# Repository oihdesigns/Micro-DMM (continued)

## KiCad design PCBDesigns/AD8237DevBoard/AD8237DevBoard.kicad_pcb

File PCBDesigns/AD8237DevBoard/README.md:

# AD8237 Sensor Development Board - Rev C

KiCad 10, 60 x 50 mm, two layers. Eight I2C-selected gains, buffered half-supply reference, 3.3 V or 5 V analog supply.

Open `AD8237DevBoard.kicad_pro`. Nick's edited PCB is the layout source. Rev C replaces U2 and adds nine resistors. Existing placements are retained except C10, moved slightly to clear the larger mux. The pre-change design is in `archive/pre-eight-gain/`.

**Prototype:** not fabricated or measured. Electrical/layout checks and ideal DC calculations do not establish measured stability, noise, settling or accuracy.

## Eight gains

U2: **TMUX1108PWR**, PW TSSOP-16, 4.4 x 5 mm body, 0.65 mm pitch. U3: **TCA9536DGKR**, I2C address **0x41**. P0/P1/P2 drive A0/A1/A2; P3 is unused. No range-bank jumper is needed.

| Code / A2 A1 A0 | Nominal gain | Upper resistor | Lower resistor | U2 channel / pin |
|---|---:|---|---|---|
| 0 / 000 | 1 | R13 2k sense resistor | None | S1 / 4 |
| 1 / 001 | 2.5 | R21 30k | R22 20k | S2 / 5 |
| 2 / 010 | 5.02 | R23 40.2k | R24 10k | S3 / 6 |
| 3 / 011 | 10.09 | R4 90.9k | R3 10k | S4 / 7 |
| 4 / 100 | 25.048096 | R25 120k | R26 4.99k | S5 / 12 |
| 5 / 101 | 49.780488 | R27 100k | R28 2.05k | S6 / 11 |
| 6 / 110 | 101 | R6 100k | R5 1k | S7 / 10 |
| 7 / 111 | 1001 | R12 1M | R11 1k | S8 / 9 |

Upper resistors run from OUT_RAW to the selected tap; lower resistors run from the tap to REF. Gain resistors are 0.1% thin film, <=25 ppm/degree C, 0805. The original 10.09/101/1001 resistor pairs are retained. The mux selects a high-impedance feedback node, keeping switch on-resistance out of the gain-setting resistor ratio.

Initialize U3 in this order:

1. Write register `0x01 = 0x00`: preload unity into the output latch.
2. Write register `0x03 = 0xF0`: P0-P3 outputs; unused P3 stays low, avoiding a floating input when pull-ups are disabled.
3. Write register `0x50 = 0x40`: disable internal port pull-ups.

Then write code 0-7 to register `0x01`, updating all selection bits together. **The code mapping changed from Rev B:** code 1 is now 2.5, not 10.09.

R17/R18/R29 are 4.7k pull-downs: the maximum specified 100 uA internal startup pull-up current produces <=0.475 V including resistor tolerance. EN is tied high; VSS is grounded. After valid supplies establish, the default is unity before software initialization. Reinitialize after VIO power cycling; a host reset alone does not reset a separately powered U3.

The Arduino Wire example is `firmware/AD8237GainExample/AD8237GainExample.ino`. It starts at unity and accepts a serial digit 0-7. Its 50 ms startup and 20 ms gain-change delays are initial bench-test allowances, not guaranteed settling times. Discard ADC samples during switching and settling. The example has not been compiled for a particular controller or tested on hardware.

## Connections

| Connector | Pins in order |
|---|---|
| J1 | 1 external regulated analog supply, 2 GND |
| J2 | 1 IN+, 2 IN-, 3 GND |
| J3 | 1 OUT after R8, 2 GND, 3 external reference |
| J4 | 1 GND, 2 host VIO supply, 3 SDA, 4 SCL |

| Jumper | Default | Alternative |
|---|---|---|
| JP1 | 2-3: analog supply from VIO | 1-2: analog supply from J1 |
| JP2 | **1-2: LOW bandwidth** | 2-3: HIGH only while gain >=10 |
| JP3 | 3-4: buffered VS/2 | 1-2: GND; 5-6: external J3 reference |
| JP4 | Fitted: 4.7k I2C pull-ups to VIO | Remove if host has suitable pull-ups |

Fit one shunt on each JP1/JP2/JP3, plus JP4 as appropriate. Change supply/reference shunts with power off. **Keep JP2 LOW for normal eight-gain operation and startup.** HIGH is unsuitable at gains 1, 2.5 and 5.02. With JP2 empty, R7 pulls BW low.

For normal 3.3 V use, power J4 VIO at 3.3 V and select JP1 2-3. For 5 V analog with a 3.3 V controller, power J1 from regulated 5 V, J4 VIO from 3.3 V, and select JP1 1-2. The mux accepts 3.3 V controls with a 5 V supply. Always match VIO to the host logic voltage. A 5 V analog output can exceed a 3.3 V ADC's input range.

## Analog behavior

`VOUT_RAW = VREF + G * (VIN+ - VIN-)`, before output resistor R8.

OPA333 U4 buffers a filtered equal-10k divider, giving about 1.65 V at VS=3.3 V or 2.5 V at VS=5 V. Selected REF drives all seven divider returns; R14 connects it to the AD8237 REF pin. External references must be low impedance and able to source and sink divider current.

The seven dividers present about 12.7k from OUT_RAW to REF. Prefer an output load of **100k or greater**: effective load is then about 11.3k, above the AD8237's recommended 10k. At 1.65 V output-reference difference, divider current is about 130 uA. R8 adds about 0.1% attenuation into 100k; TP5 senses before R8. Individual feedback divider Thevenin resistances are below 30k.

At gain 1001 and REF=1.65 V, +/-1 mV differential input ideally gives 0.649-2.651 V output. Both physical inputs must remain within supply limits. Allow output headroom and calibrate for resistor ratios, temperature and amplifier/load errors.

C7 stays fitted at 470 pF C0G, following AD8237 Figure 76. The TMUX1108 has higher feedback-node capacitance than the former mux. LOW bandwidth is the baseline; bench-check overshoot, oscillation and settling at every gain. No device-level transient simulation or measured stability margin is claimed.

C3-C6 and R9/R10 are DNP by default. They provide optional filters and input bias-current returns. Floating sensors need an appropriate DC return. C7 and the remaining resistors/capacitors are fitted.

## Deliverables and checks

- `docs/AD8237DevBoard-schematic.pdf`: current schematic.
- `docs/ERC.json`, `docs/DRC.json`, `docs/design-verification.json`: electrical, routing/parity and independent pin/gain verification.
- `manufacturing/BOM.csv`, `manufacturing/placement.csv`: current assembly data.
- `manufacturing/AD8237DevBoard-RevC-Gerbers.zip`: current fabrication package.
- `manufacturing/stencil/`: paste with DNP parts omitted.

General routing uses 0.20 mm tracks/clearance. A local 0.15 mm pad-clearance override on U3 accommodates that standard package's pad gaps. Other footprints retain the project clearance rule.

`scripts/export.ps1` checks and exports the edited board. `scripts/design.py` regenerates the schematic from component data, preserving existing project settings; it does not ingest manual schematic changes. The old full-board builder is disabled to protect the edited PCB. The one-time migration writes only a draft under `tmp/eight-gain/`.

## Datasheet references

- [AD8237](https://www.analog.com/media/en/technical-documentation/data-sheets/ad8237.pdf): pinout p8, gain/BW p20, programmable gain Figure 76 p25.
- [TMUX1108](https://www.ti.com/lit/ds/symlink/tmux1108.pdf): PW pinout p2-3, supply and logic ratings, truth table p23.
- [TCA9536](https://www.ti.com/lit/ds/symlink/tca9536.pdf): DGK pins, startup pull-ups, address and registers p19-20.
- [OPA333](https://www.ti.com/lit/ds/symlink/opa333.pdf): SOT-23 pinout and buffer operation.

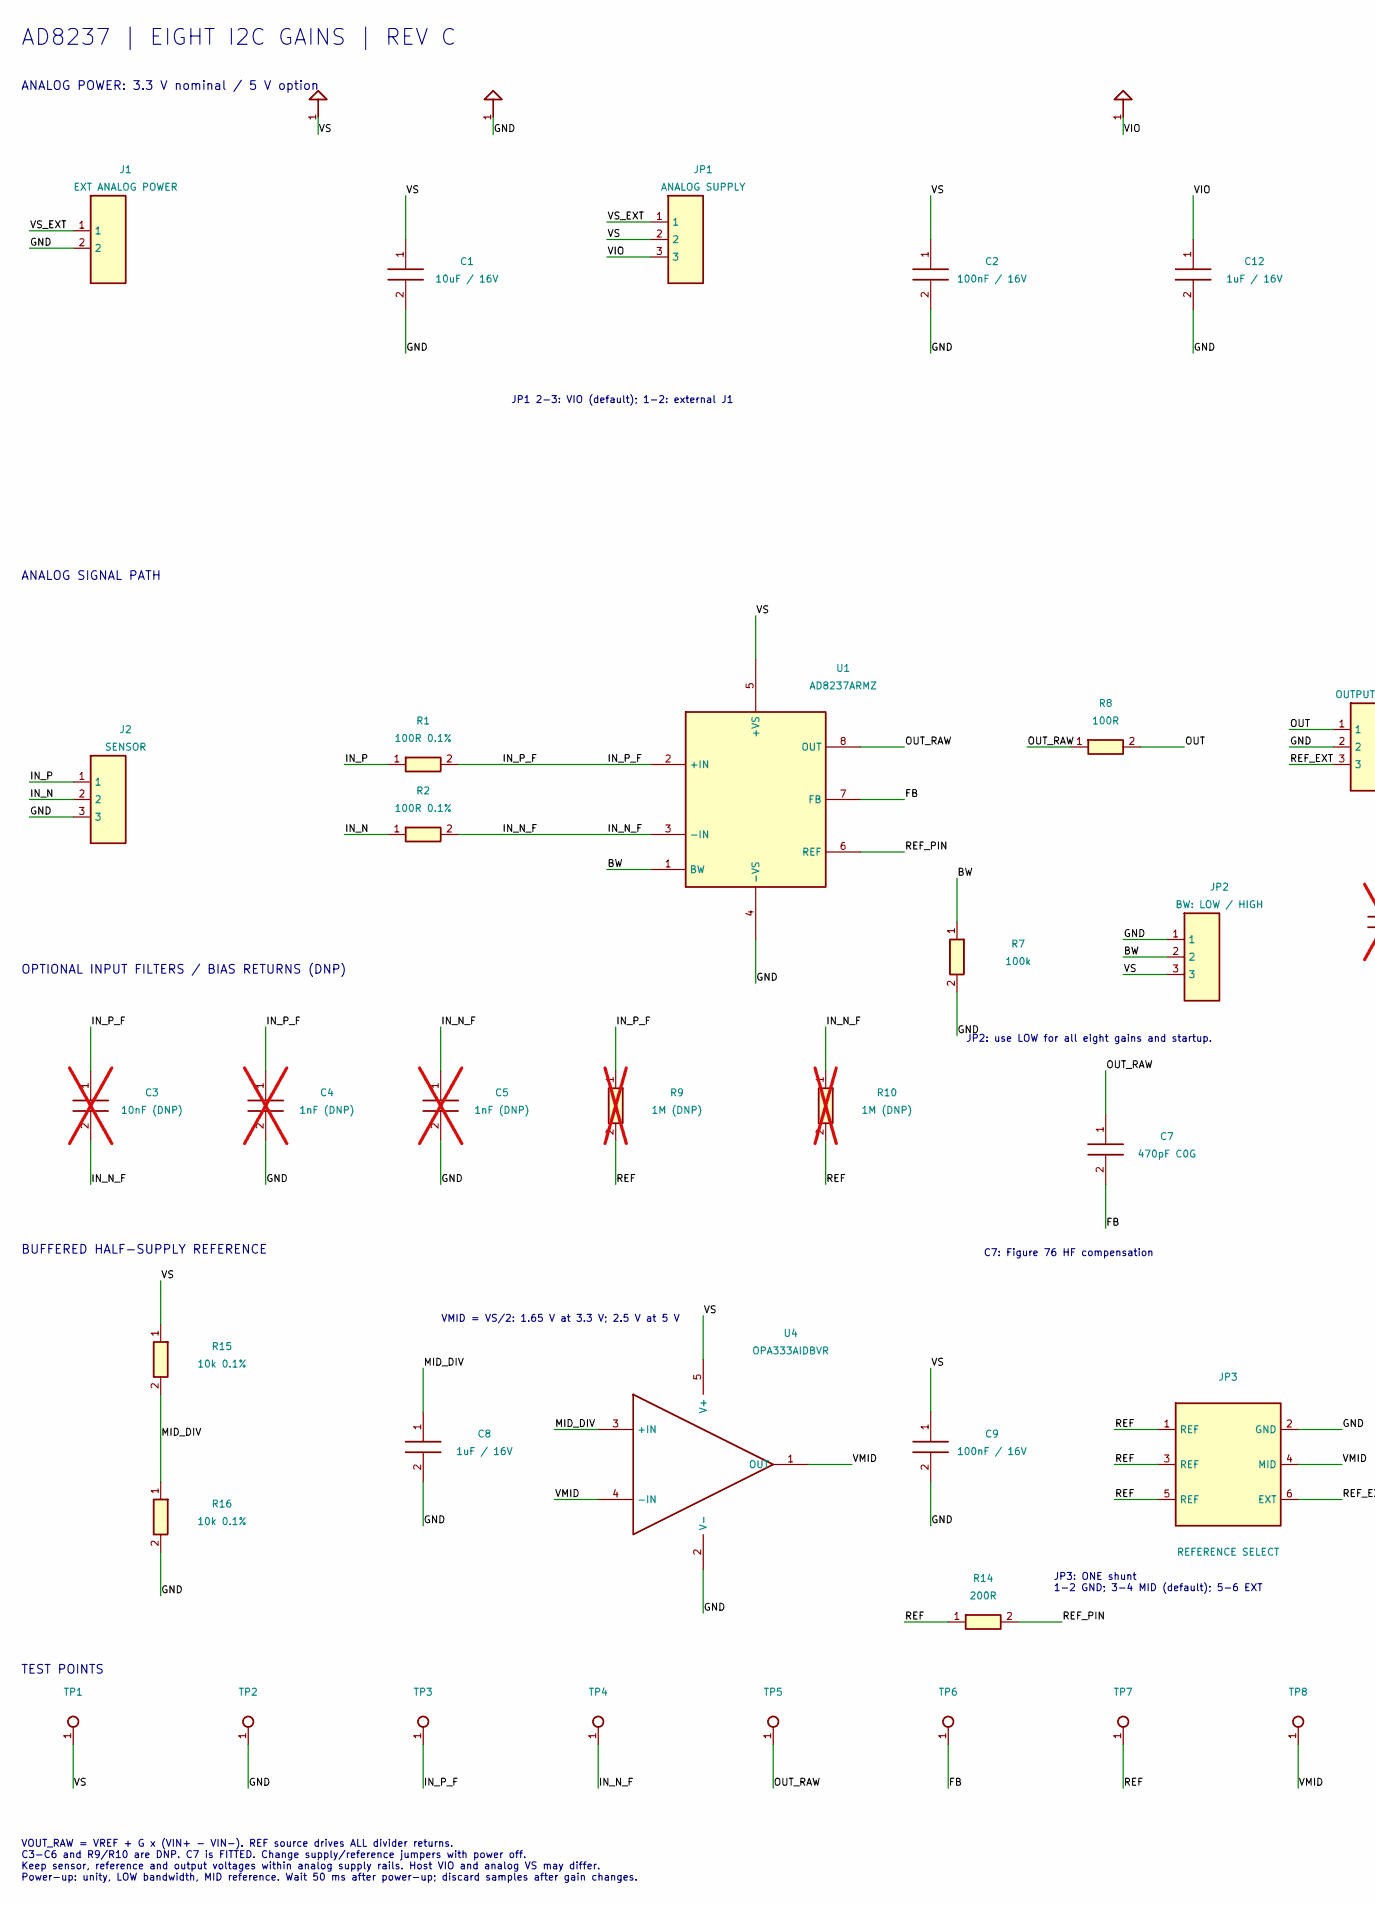
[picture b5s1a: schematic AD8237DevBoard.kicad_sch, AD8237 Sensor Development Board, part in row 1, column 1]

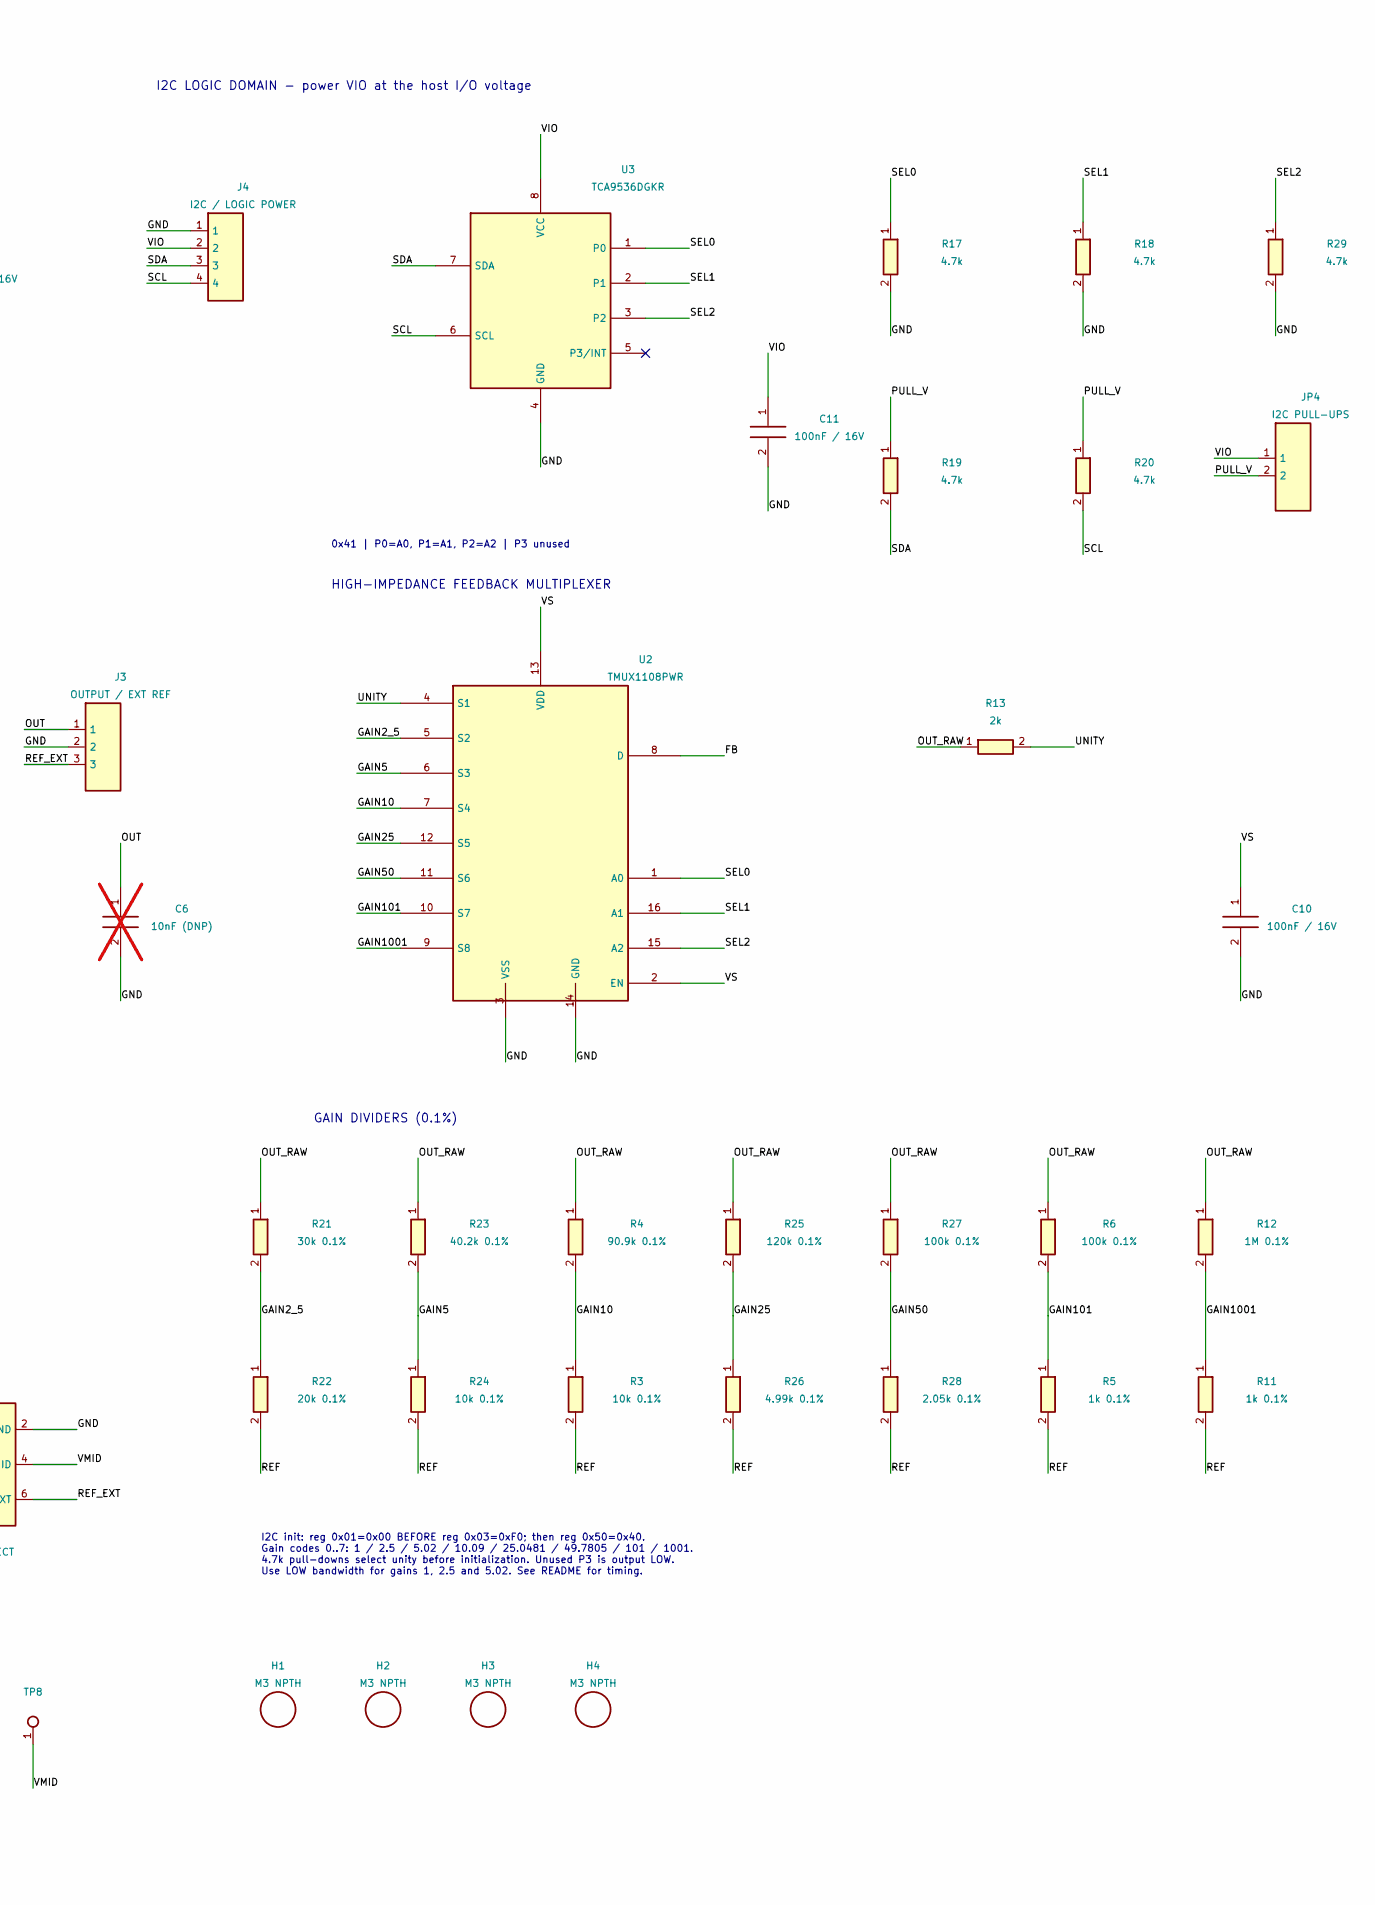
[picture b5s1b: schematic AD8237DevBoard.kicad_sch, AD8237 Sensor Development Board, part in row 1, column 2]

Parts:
C1: 10uF / 16V; C_0805_2012Metric
C2, C9, C10, C11: 100nF / 16V; C_0805_2012Metric
C3, C6: 10nF (DNP); C_0805_2012Metric; not fitted
C4, C5: 1nF (DNP); C_0805_2012Metric; not fitted
C7: 470pF C0G; C_0805_2012Metric
C8, C12: 1uF / 16V; C_0805_2012Metric
H1, H2, H3, H4: M3 NPTH; MountingHole_3.2mm_M3
J1: EXT ANALOG POWER; PinHeader_1x02_P2.54mm_Vertical
J2: SENSOR; PinHeader_1x03_P2.54mm_Vertical
J3: OUTPUT / EXT REF; PinHeader_1x03_P2.54mm_Vertical
J4: I2C / LOGIC POWER; PinHeader_1x04_P2.54mm_Vertical
JP1: ANALOG SUPPLY; PinHeader_1x03_P2.54mm_Vertical
JP2: BW: LOW / HIGH; PinHeader_1x03_P2.54mm_Vertical
JP3: REFERENCE SELECT; PinHeader_2x03_P2.54mm_Vertical
JP4: I2C PULL-UPS; PinHeader_1x02_P2.54mm_Vertical
R1, R2: 100R 0.1%; R_0805_2012Metric
R3, R15, R16, R24: 10k 0.1%; R_0805_2012Metric
R4: 90.9k 0.1%; R_0805_2012Metric
R5, R11: 1k 0.1%; R_0805_2012Metric
R6, R27: 100k 0.1%; R_0805_2012Metric
R7: 100k; R_0805_2012Metric
R8: 100R; R_0805_2012Metric
R9, R10: 1M (DNP); R_0805_2012Metric; not fitted
R12: 1M 0.1%; R_0805_2012Metric
R13: 2k; R_0805_2012Metric
R14: 200R; R_0805_2012Metric
R17, R18, R19, R20, R29: 4.7k; R_0805_2012Metric
R21: 30k 0.1%; R_0805_2012Metric
R22: 20k 0.1%; R_0805_2012Metric
R23: 40.2k 0.1%; R_0805_2012Metric
R25: 120k 0.1%; R_0805_2012Metric
R26: 4.99k 0.1%; R_0805_2012Metric
R28: 2.05k 0.1%; R_0805_2012Metric
TP1: VS; TestPoint_Pad_D1.5mm
TP2: GND; TestPoint_Pad_D1.5mm
TP3: IN_P_F; TestPoint_Pad_D1.5mm
TP4: IN_N_F; TestPoint_Pad_D1.5mm
TP5: OUT_RAW; TestPoint_Pad_D1.5mm
TP6: FB; TestPoint_Pad_D1.5mm
TP7: REF; TestPoint_Pad_D1.5mm
TP8: VMID; TestPoint_Pad_D1.5mm
U1: AD8237ARMZ; MSOP-8_3x3mm_P0.65mm
U2: TMUX1108PWR; TSSOP-16_4.4x5mm_P0.65mm
U3: TCA9536DGKR; VSSOP-8_3x3mm_P0.65mm
U4: OPA333AIDBVR; SOT-23-5

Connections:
/BW: JP2.2, R7.1, U1.1 (BW)
/FB: C7.2, TP6.1, U1.7 (FB), U2.8 (D)
/GAIN2_5: R21.2, R22.1, U2.5 (S2)
/GAIN5: R23.2, R24.1, U2.6 (S3)
/GAIN10: R3.1, R4.2, U2.7 (S4)
/GAIN25: R25.2, R26.1, U2.12 (S5)
/GAIN50: R27.2, R28.1, U2.11 (S6)
/GAIN101: R5.1, R6.2, U2.10 (S7)
/GAIN1001: R11.1, R12.2, U2.9 (S8)
/GND: C1.2, C2.2, C4.2, C5.2, C6.2, C8.2, C9.2, C10.2, C11.2, C12.2, J1.2, J2.3, J3.2, J4.1, JP2.1, JP3.2 (GND), R7.2, R16.2, R17.2, R18.2, R29.2, TP2.1, U1.4 (-VS), U2.3 (VSS), U2.14 (GND), U3.4 (GND), U4.2 (V-)
/IN_N: J2.2, R2.1
/IN_N_F: C3.2, C5.1, R2.2, R10.1, TP4.1, U1.3 (-IN)
/IN_P: J2.1, R1.1
/IN_P_F: C3.1, C4.1, R1.2, R9.1, TP3.1, U1.2 (+IN)
/MID_DIV: C8.1, R15.2, R16.1, U4.3 (+IN)
/OUT: C6.1, J3.1, R8.2
/OUT_RAW: C7.1, R4.1, R6.1, R8.1, R12.1, R13.1, R21.1, R23.1, R25.1, R27.1, TP5.1, U1.8 (OUT)
/PULL_V: JP4.2, R19.1, R20.1
/REF: JP3.1 (REF), JP3.3 (REF), JP3.5 (REF), R3.2, R5.2, R9.2, R10.2, R11.2, R14.1, R22.2, R24.2, R26.2, R28.2, TP7.1
/REF_EXT: J3.3, JP3.6 (EXT)
/REF_PIN: R14.2, U1.6 (REF)
/SCL: J4.4, R20.2, U3.6 (SCL)
/SDA: J4.3, R19.2, U3.7 (SDA)
/SEL0: R17.1, U2.1 (A0), U3.1 (P0)
/SEL1: R18.1, U2.16 (A1), U3.2 (P1)
/SEL2: R29.1, U2.15 (A2), U3.3 (P2)
/UNITY: R13.2, U2.4 (S1)
/VIO: C11.1, C12.1, J4.2, JP1.3, JP4.1, U3.8 (VCC)
/VMID: JP3.4 (MID), TP8.1, U4.1 (OUT), U4.4 (-IN)
/VS: C1.1, C2.1, C9.1, C10.1, JP1.2, JP2.3, R15.1, TP1.1, U1.5 (+VS), U2.2 (EN), U2.13 (VDD), U4.5 (V+)
/VS_EXT: J1.1, JP1.1

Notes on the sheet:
AD8237 | EIGHT I2C GAINS | REV C
ANALOG POWER: 3.3 V nominal / 5 V option
JP1 2-3: VIO (default); 1-2: external J1
I2C LOGIC DOMAIN - power VIO at the host I/O voltage
0x41 | P0=A0, P1=A1, P2=A2 | P3 unused
ANALOG SIGNAL PATH
HIGH-IMPEDANCE FEEDBACK MULTIPLEXER
JP2: use LOW for all eight gains and startup.
OPTIONAL INPUT FILTERS / BIAS RETURNS (DNP)
C7: Figure 76 HF compensation
GAIN DIVIDERS (0.1%)
BUFFERED HALF-SUPPLY REFERENCE
VMID = VS/2: 1.65 V at 3.3 V; 2.5 V at 5 V
JP3: ONE shunt 1-2 GND; 3-4 MID (default); 5-6 EXT
I2C init: reg 0x01=0x00 BEFORE reg 0x03=0xF0; then reg 0x50=0x40. Gain codes 0..7: 1 / 2.5 / 5.02 / 10.09 / 25.0481 / 49.7805 / 101 / 1001. 4.7k pull-downs select unity before initialization. Unused P3 is output LOW. Use LOW bandwidth for gains 1, 2.5 and 5.02. See README for timing.
TEST POINTS
VOUT_RAW = VREF + G x (VIN+ - VIN-). REF source drives ALL divider returns. C3-C6 and R9/R10 are DNP. C7 is FITTED. Change supply/reference jumpers with power off. Keep sensor, reference and output voltages within analog supply rails. Host VIO and analog VS may differ. Power-up: unity, LOW bandwidt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

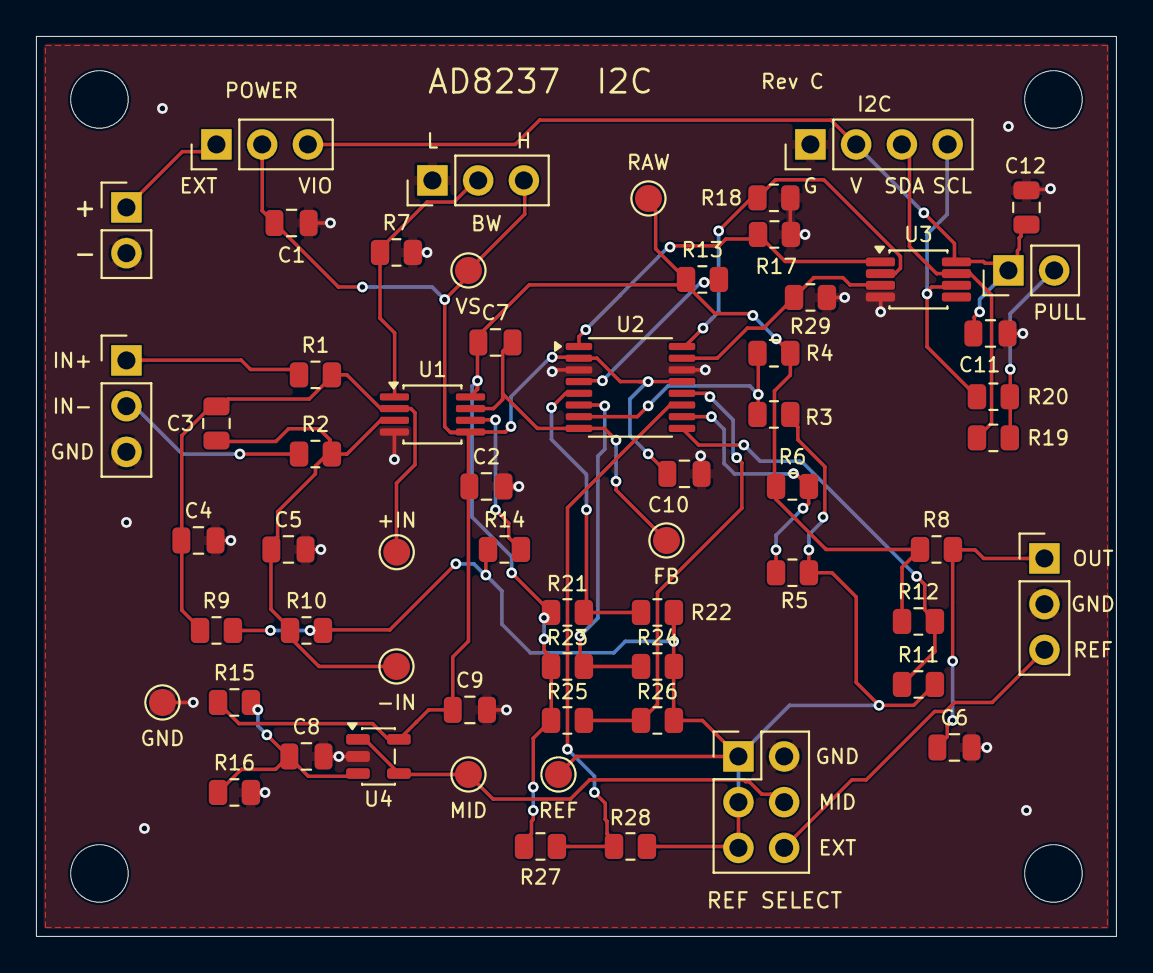
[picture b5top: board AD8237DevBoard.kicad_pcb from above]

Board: 2 copper layers, 60.0 x 50.0 mm, 65 parts (0 on the bottom side), 31 nets.

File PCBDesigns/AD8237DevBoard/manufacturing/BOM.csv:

Reference,Value,Footprint,Fit,Specification / assembly note
U1,AD8237ARMZ,AD8237DevBoard:MSOP-8_3x3mm_P0.65mm,YES,"Analog Devices AD8237ARMZ, RM-8"
U2,TMUX1108PWR,AD8237DevBoard:TSSOP-16_4.4x5mm_P0.65mm,YES,"TI TMUX1108PWR, PW TSSOP-16; EN tied high; VSS tied GND; fail-safe logic"
U3,TCA9536DGKR,AD8237DevBoard:VSSOP-8_3x3mm_P0.65mm,YES,TI TCA9536DGKR; I2C 7-bit address 0x41; P0-P2 select gain; P3 unused
U4,OPA333AIDBVR,AD8237DevBoard:SOT-23-5,YES,"TI OPA333AIDBVR, SOT-23-5; unity-gain midpoint buffer"
J1,EXT ANALOG POWER,AD8237DevBoard:PinHeader_1x02_P2.54mm_Vertical,YES,External regulated analog supply input; select JP1 EXT
J2,SENSOR,AD8237DevBoard:PinHeader_1x03_P2.54mm_Vertical,YES,"1 IN+, 2 IN-, 3 GND"
J3,OUTPUT / EXT REF,AD8237DevBoard:PinHeader_1x03_P2.54mm_Vertical,YES,"1 OUT after R8, 2 GND, 3 external reference input"
J4,I2C / LOGIC POWER,AD8237DevBoard:PinHeader_1x04_P2.54mm_Vertical,YES,"1 GND, 2 VIO input (host 3.3 V or 5 V), 3 SDA, 4 SCL; match VIO to host"
JP1,ANALOG SUPPLY,AD8237DevBoard:PinHeader_1x03_P2.54mm_Vertical,YES,ONE shunt: 2-3 default powers analog from VIO; 1-2 selects external J1 supply
JP2,BW: LOW / HIGH,AD8237DevBoard:PinHeader_1x03_P2.54mm_Vertical,YES,"1-2 LOW default, valid for every gain. 2-3 HIGH requires gain >=10, including at startup"
JP3,REFERENCE SELECT,AD8237DevBoard:PinHeader_2x03_P2.54mm_Vertical,YES,ONE shunt: 1-2 GND; 3-4 MID default; 5-6 external J3.3
JP4,I2C PULL-UPS,AD8237DevBoard:PinHeader_1x02_P2.54mm_Vertical,YES,Fit shunt to enable 4.7k pull-ups to VIO. Remove when host provides sufficient pull-ups
R1,100R 0.1%,AD8237DevBoard:R_0805_2012Metric,YES,"Thin film, 0.1%, <=25 ppm/C"
R2,100R 0.1%,AD8237DevBoard:R_0805_2012Metric,YES,"Thin film, 0.1%, <=25 ppm/C"
R3,10k 0.1%,AD8237DevBoard:R_0805_2012Metric,YES,"Thin film, 0.1%, <=25 ppm/C"
R4,90.9k 0.1%,AD8237DevBoard:R_0805_2012Metric,YES,"Thin film, 0.1%, <=25 ppm/C"
R5,1k 0.1%,AD8237DevBoard:R_0805_2012Metric,YES,"Thin film, 0.1%, <=25 ppm/C"
R6,100k 0.1%,AD8237DevBoard:R_0805_2012Metric,YES,"Thin film, 0.1%, <=25 ppm/C"
R7,100k,AD8237DevBoard:R_0805_2012Metric,YES,"1%, 0805"
R8,100R,AD8237DevBoard:R_0805_2012Metric,YES,"1%, 0805"
R9,1M (DNP),AD8237DevBoard:R_0805_2012Metric,DNP,Optional sensor DC bias return to selected REF; not fitted
R10,1M (DNP),AD8237DevBoard:R_0805_2012Metric,DNP,Optional sensor DC bias return to selected REF; not fitted
R11,1k 0.1%,AD8237DevBoard:R_0805_2012Metric,YES,"Thin film, 0.1%, <=25 ppm/C"
R12,1M 0.1%,AD8237DevBoard:R_0805_2012Metric,YES,"Thin film, 0.1%, <=25 ppm/C"
R13,2k,AD8237DevBoard:R_0805_2012Metric,YES,"Unity sense series resistor, as in AD8237 Figure 76"
R14,200R,AD8237DevBoard:R_0805_2012Metric,YES,REF input bias compensation; divider returns use REF before this resistor
R15,10k 0.1%,AD8237DevBoard:R_0805_2012Metric,YES,"Thin film, 0.1%, <=25 ppm/C"
R16,10k 0.1%,AD8237DevBoard:R_0805_2012Metric,YES,"Thin film, 0.1%, <=25 ppm/C"
R17,4.7k,AD8237DevBoard:R_0805_2012Metric,YES,1% pull-down: <=0.475 V with expander maximum 100 uA internal pull-up; default unity
R18,4.7k,AD8237DevBoard:R_0805_2012Metric,YES,1% pull-down: <=0.475 V with expander maximum 100 uA internal pull-up; default unity
R19,4.7k,AD8237DevBoard:R_0805_2012Metric,YES,"1%, 0805"
R20,4.7k,AD8237DevBoard:R_0805_2012Metric,YES,"1%, 0805"
R21,30k 0.1%,AD8237DevBoard:R_0805_2012Metric,YES,"Thin film, 0.1%, <=25 ppm/C"
R22,20k 0.1%,AD8237DevBoard:R_0805_2012Metric,YES,"Thin film, 0.1%, <=25 ppm/C"
R23,40.2k 0.1%,AD8237DevBoard:R_0805_2012Metric,YES,"Thin film, 0.1%, <=25 ppm/C"
R24,10k 0.1%,AD8237DevBoard:R_0805_2012Metric,YES,"Thin film, 0.1%, <=25 ppm/C"
R25,120k 0.1%,AD8237DevBoard:R_0805_2012Metric,YES,"Thin film, 0.1%, <=25 ppm/C"
R26,4.99k 0.1%,AD8237DevBoard:R_0805_2012Metric,YES,"Thin film, 0.1%, <=25 ppm/C"
R27,100k 0.1%,AD8237DevBoard:R_0805_2012Metric,YES,"Thin film, 0.1%, <=25 ppm/C"
R28,2.05k 0.1%,AD8237DevBoard:R_0805_2012Metric,YES,"Thin film, 0.1%, <=25 ppm/C"
R29,4.7k,AD8237DevBoard:R_0805_2012Metric,YES,1% pull-down: <=0.475 V with expander maximum 100 uA internal pull-up; default unity
C1,10uF / 16V,AD8237DevBoard:C_0805_2012Metric,YES,"X7R, 16 V; local supply bypass"
C2,100nF / 16V,AD8237DevBoard:C_0805_2012Metric,YES,"X7R, 16 V; local supply bypass"
C3,10nF (DNP),AD8237DevBoard:C_0805_2012Metric,DNP,DNP; optional C0G filter; match C4/C5 1% if populated
C4,1nF (DNP),AD8237DevBoard:C_0805_2012Metric,DNP,DNP; optional C0G filter; match C4/C5 1% if populated
C5,1nF (DNP),AD8237DevBoard:C_0805_2012Metric,DNP,DNP; optional C0G filter; match C4/C5 1% if populated
C6,10nF (DNP),AD8237DevBoard:C_0805_2012Metric,DNP,DNP; optional C0G filter; match C4/C5 1% if populated
C7,470pF C0G,AD8237DevBoard:C_0805_2012Metric,YES,"C0G 5%, >=16 V; high-frequency feedback compensation, AD8237 Figure 76"
C8,1uF / 16V,AD8237DevBoard:C_0805_2012Metric,YES,"X7R 16 V; midpoint divider filter, nominal 5 ms time constant"
C9,100nF / 16V,AD8237DevBoard:C_0805_2012Metric,YES,"X7R, 16 V; local supply bypass"
C10,100nF / 16V,AD8237DevBoard:C_0805_2012Metric,YES,"X7R, 16 V; local supply bypass"
C11,100nF / 16V,AD8237DevBoard:C_0805_2012Metric,YES,"X7R, 16 V; local supply bypass"
C12,1uF / 16V,AD8237DevBoard:C_0805_2012Metric,YES,"X7R, 16 V; local supply bypass"
TP1,VS,AD8237DevBoard:TestPoint_Pad_D1.5mm,PCB feature,Exposed 1.5 mm probe pad
TP2,GND,AD8237DevBoard:TestPoint_Pad_D1.5mm,PCB feature,Exposed 1.5 mm probe pad
TP3,IN_P_F,AD8237DevBoard:TestPoint_Pad_D1.5mm,PCB feature,Exposed 1.5 mm probe pad
TP4,IN_N_F,AD8237DevBoard:TestPoint_Pad_D1.5mm,PCB feature,Exposed 1.5 mm probe pad
TP5,OUT_RAW,AD8237DevBoard:TestPoint_Pad_D1.5mm,PCB feature,Exposed 1.5 mm probe pad
TP6,FB,AD8237DevBoard:TestPoint_Pad_D1.5mm,PCB feature,Exposed 1.5 mm probe pad
TP7,REF,AD8237DevBoard:TestPoint_Pad_D1.5mm,PCB feature,Exposed 1.5 mm probe pad
TP8,VMID,AD8237DevBoard:TestPoint_Pad_D1.5mm,PCB feature,Exposed 1.5 mm probe pad
H1,M3 NPTH,AD8237DevBoard:MountingHole_3.2mm_M3,PCB feature,3.2 mm non-plated mounting hole
H2,M3 NPTH,AD8237DevBoard:MountingHole_3.2mm_M3,PCB feature,3.2 mm non-plated mounting hole
H3,M3 NPTH,AD8237DevBoard:MountingHole_3.2mm_M3,PCB feature,3.2 mm non-plated mounting hole
H4,M3 NPTH,AD8237DevBoard:MountingHole_3.2mm_M3,PCB feature,3.2 mm non-plated mounting hole
SH1-SH4,2.54 mm jumper shunt,Accessory,YES,"Four shunts: JP1 2-3 (VIO), JP2 1-2 (LOW), JP3 3-4 (MID), JP4 1-2 (pull-ups enabled)"
